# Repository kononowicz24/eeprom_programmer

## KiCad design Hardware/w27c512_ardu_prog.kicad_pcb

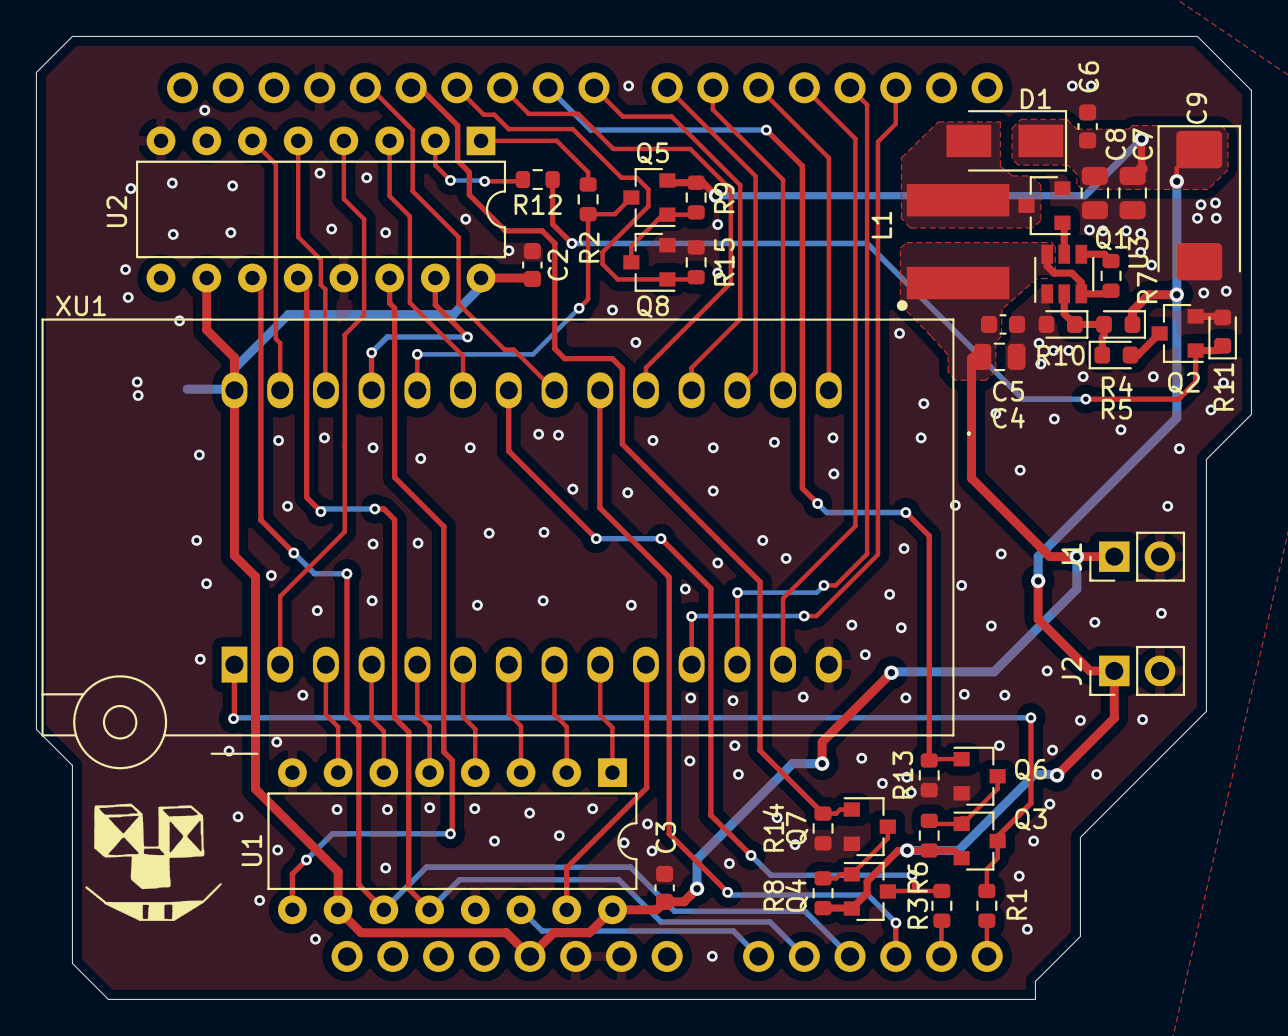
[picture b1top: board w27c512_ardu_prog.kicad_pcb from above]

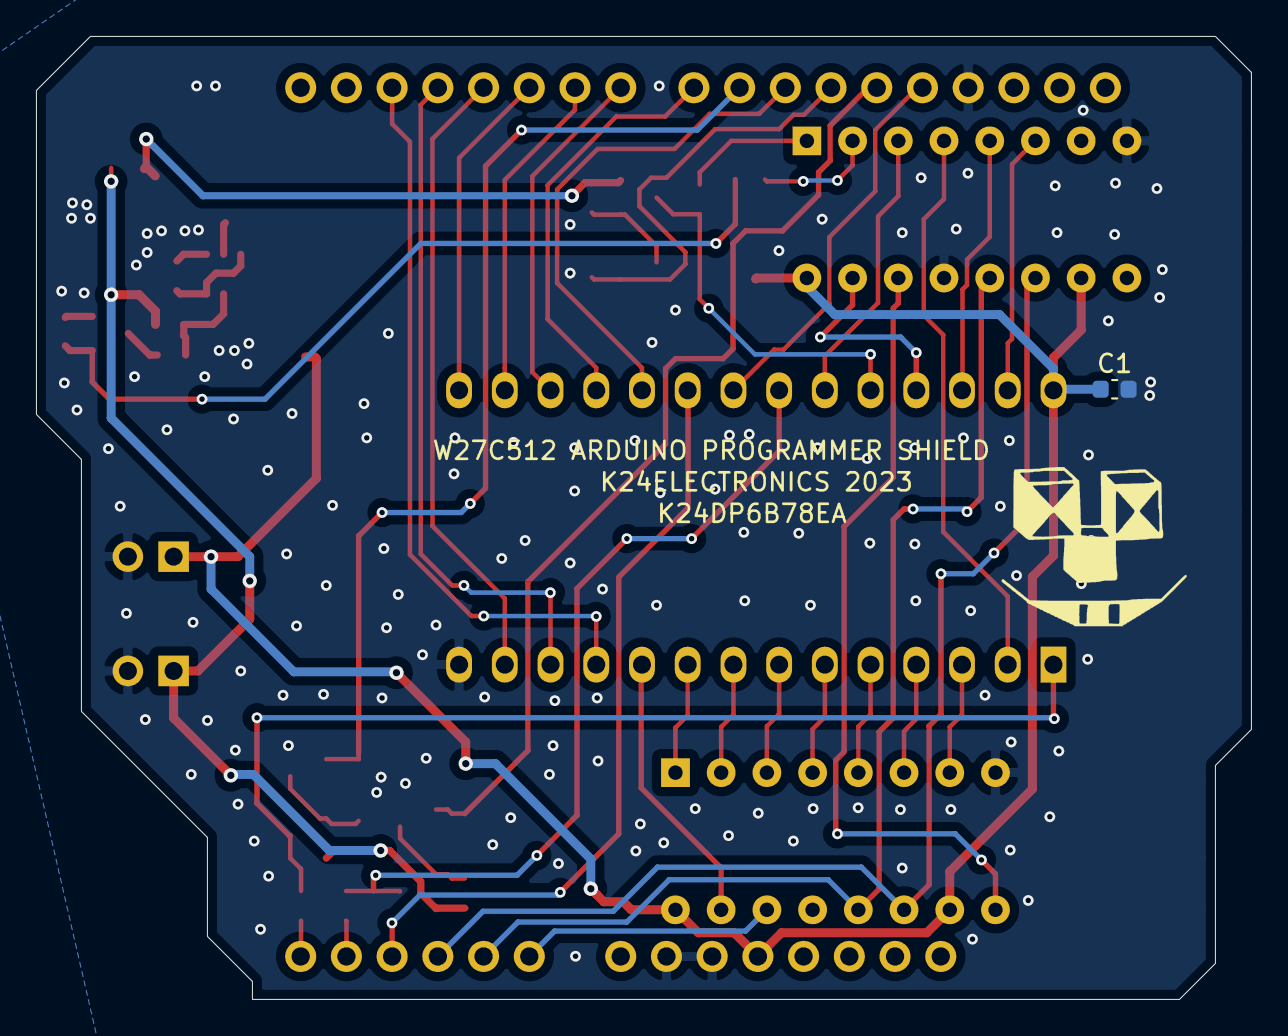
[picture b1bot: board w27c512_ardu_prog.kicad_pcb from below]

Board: 2 copper layers, 67.5 x 53.5 mm, 42 parts (2 on the bottom side), 49 nets.

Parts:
C1, C2, C3, C5, C6: C; C_0603_1608Metric
C4, C7, C8: C; C_0805_2012Metric
C9: CP; CP_EIA-7343-30_AVX-N
D1: D_Schottky; D_SMA
E: LOGO; logo_13
J1, J2: Conn_01x02_Male; PinHeader_1x02_P2.54mm_Vertical
L1: L; WE_LQS_6028
Q1, Q2, Q6, Q7, Q8: AO3400A; SOT-23
Q3, Q4, Q5: AO3401A; SOT-23
R1, R2, R3, R7: 1k; R_0603_1608Metric
R4: 130k; LED_0603_1608Metric
R5: 82k; LED_0603_1608Metric
R6, R8, R9, R13, R14, R15: 10k; R_0603_1608Metric
R10: 15k; LED_0603_1608Metric
R11: 10k; LED_0603_1608Metric
R12: 0R; R_0603_1608Metric
U1, U2: 74HC595; DIP-16_W7.62mm
U3: MAX1522EUT+T; SOT-23-6
XA1: Arduino_Uno_Shield
XU1: 27C512; DIP_Socket-28_W11.9_W12.7_W15.24_W17.78_W18.5_3M_228-1277-0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

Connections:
+5V: C1.1, C2.1, C3.1, C4.1, C5.1, J1.1, L1.1, R7.2, U1.10, U1.16, U2.10, U2.16, U3.3, U3.6, XA1.5V1, XU1.28
+12V: C6.2, C7.2, C8.2, C9.1, D1.1, J2.1, Q3.2, Q4.2, Q5.2, R4.1, R6.2, R8.2, R9.2
/D0: XA1.D2, XU1.11
/D1: XA1.D3, XU1.12
/D2: XA1.D4, XU1.13
/D3: XA1.D5, XU1.15
/D4: XA1.D6, XU1.16
/D5: XA1.D7, XU1.17
/D6: XA1.D8, XU1.18
/D7: XA1.D10, XU1.19
/FB14EN: Q2.1, R11.1, R12.1
/\CE: XA1.A3, XU1.20
/\OE: Q4.3, R3.1, XU1.22
GND: C1.2, C2.2, C3.2, C4.2, C5.2, C6.1, C7.1, C8.1, C9.2, J1.2, J2.2, Q1.2, Q2.2, Q6.2, Q7.2, Q8.2, R10.2, R11.2, R13.1, R14.1, R15.1, U1.8, U1.13, U2.8, U2.13, U3.1, XA1.GND1, XA1.GND2, XA1.GND3, XU1.14
unnamed: D1.2, L1.2, Q1.3
unnamed: Q1.1, U3.5
unnamed: Q2.3, R5.2
unnamed: Q3.1, Q6.3, R6.1
unnamed: Q3.3, R1.1, XU1.1
unnamed: Q4.1, Q7.3, R8.1
unnamed: Q5.1, Q8.3, R9.1
unnamed: Q5.3, R2.1, XU1.24
unnamed: Q6.1, R13.2, XA1.D9
unnamed: Q7.1, R14.2, XA1.D12
unnamed: Q8.1, R15.2, XA1.D11
unnamed: R1.2, XA1.A5
unnamed: R2.2, U2.1
unnamed: R3.2, XA1.A4
unnamed: R7.1, U3.4
unnamed: R4.2, R5.1, R10.1, U3.2
unnamed: R12.2, U2.2
unnamed: U1.1, XU1.9
unnamed: U1.2, XU1.8
unnamed: U1.3, XU1.7
unnamed: U1.4, XU1.6
unnamed: U1.5, XU1.5
unnamed: U1.6, XU1.4
unnamed: U1.7, XU1.3
unnamed: U1.9, U2.14
unnamed: U1.11, U2.11, XA1.A2
unnamed: U1.12, U2.12, XA1.A1
unnamed: U1.14, XA1.A0
unnamed: U1.15, XU1.10
unnamed: U2.3, XU1.23
unnamed: U2.4, XU1.2
unnamed: U2.5, XU1.26
unnamed: U2.6, XU1.27
unnamed: U2.15, XU1.25
unnamed: XA1.D13, XU1.21

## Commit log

2023-05-20 Fixed not working erase, added ability to read all W27C512 chip at once
2023-05-20 Added Kicad design for an Arduino shield.
